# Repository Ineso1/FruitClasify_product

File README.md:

# FruitClasify_product
Creación de un sistema industrial, con el cual se puedan analizar variedad de frutas, para después asignarlas a una categoría por medio de una clasificación bajo ciertos parámetros/características que estas vayan cumpliendo durante el proceso.

**Demo proyecto**
https://drive.google.com/drive/folders/1sFi9FZ5CYVEdVZt0g3_yMmRyJmRK-tTw?usp=sharing

**Sistema camara y sensores**<br></br>!

**Circuito Logico** <br></br>
diseño y simulacion de circuito logico utilizando logica combinacional y logica secuencial con flipflop, multiplexores y full adders

**Cloud computing para procesamiento de imagen**<br></br>
Se crea un servicio con Nodejs para la escucha de peticiones de procesamiento de imagen para la obtencion del tamaño (diametro y area), porcentage BGR de las matrices de colores de la imagen
El procesamiento de imagen se realiza generando un hilo como subproceso del servidor ejecutando scripts de python con OpenCV

**Sistema fisico**
Trasporte por medio de banda transportadora

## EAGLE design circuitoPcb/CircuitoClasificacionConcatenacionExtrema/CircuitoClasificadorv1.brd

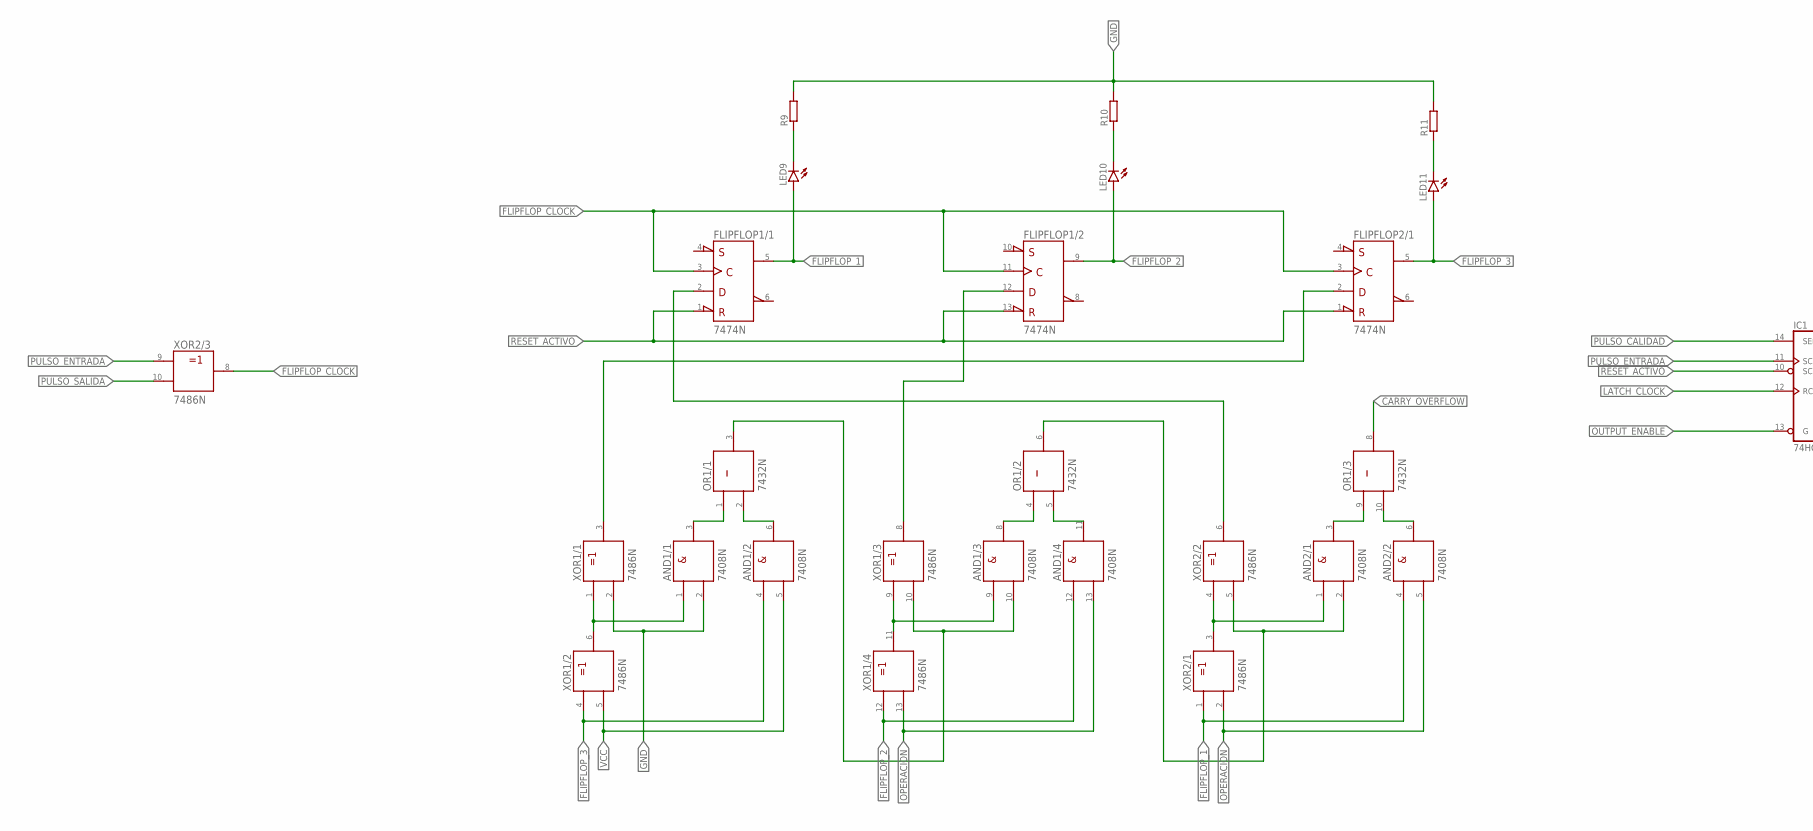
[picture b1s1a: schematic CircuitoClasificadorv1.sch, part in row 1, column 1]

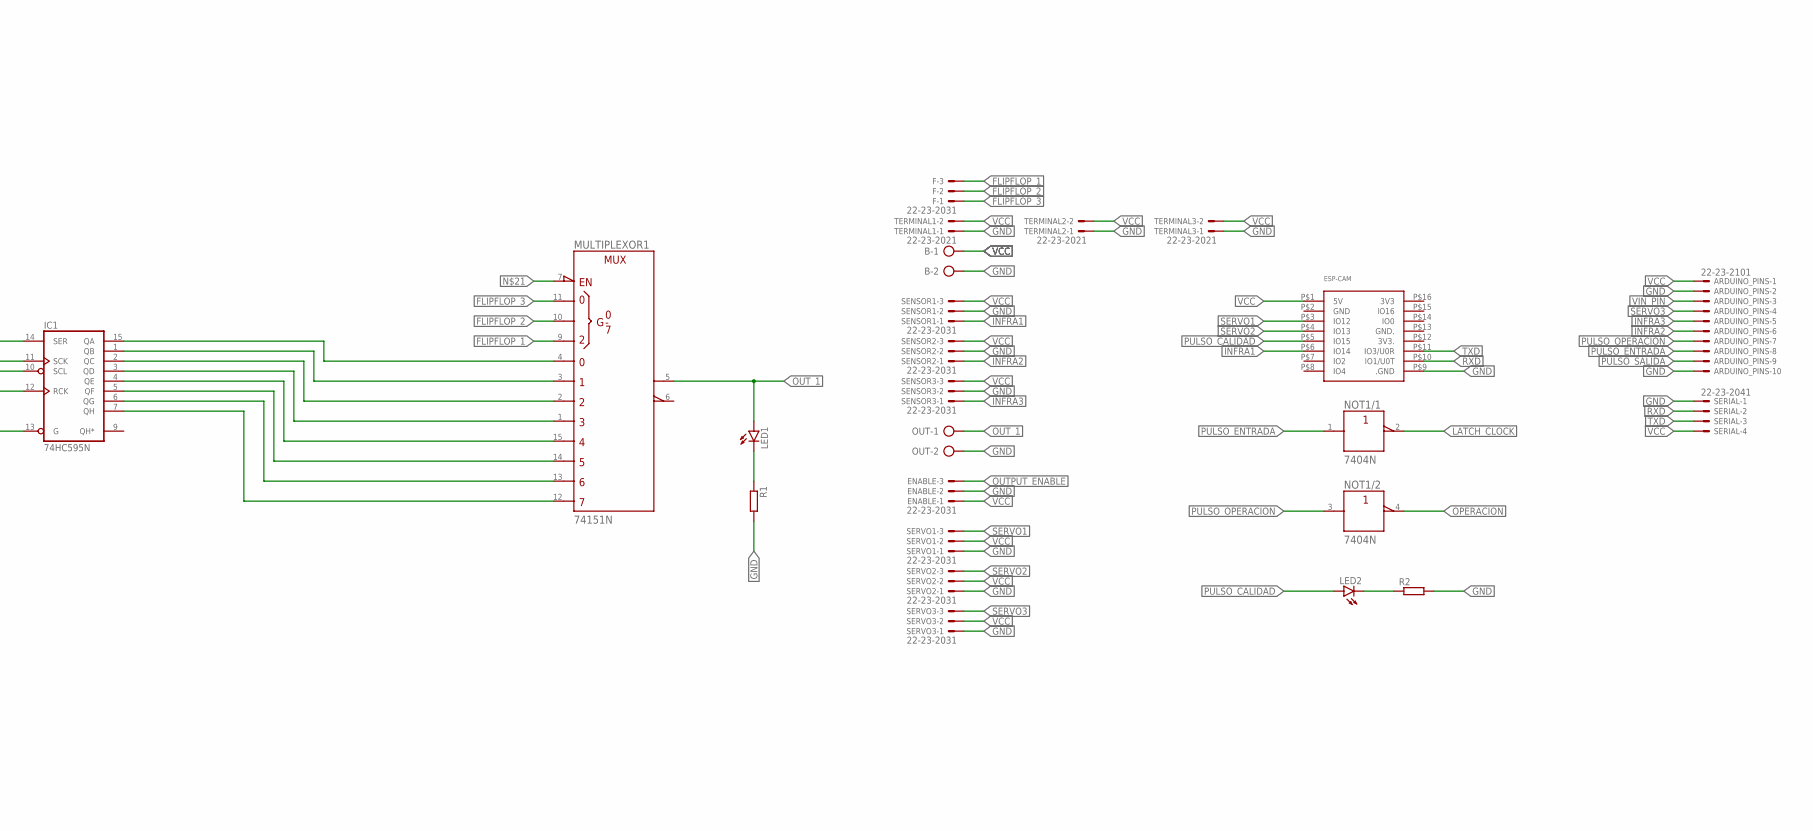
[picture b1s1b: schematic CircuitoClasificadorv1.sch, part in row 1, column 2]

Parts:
AND1, AND2: 7408N; DIL14
ARDUINO_PINS: 22-23-2101
B: AK500/2
ENABLE: 22-23-2031
ESP-CAM: ESP32-CAM
F: 22-23-2031
FLIPFLOP1, FLIPFLOP2: 7474N; DIL14
IC1: 74HC595N; DIL16
LED1, LED2, LED9, LED10, LED11: LED5MM
MULTIPLEXOR1: 74151N; DIL16
NOT1: 7404N; DIL14
OR1: 7432N; DIL14
OUT: AK500/2-H
R1, R2, R9, R10, R11: R-EU_0207/10; 0207/10
SENSOR1, SENSOR2, SENSOR3: 22-23-2031
SERIAL: 22-23-2041
SERVO1, SERVO2, SERVO3: 22-23-2031
TERMINAL1, TERMINAL2, TERMINAL3: 22-23-2021
XOR1, XOR2: 7486N; DIL14

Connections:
+UB: AND1.14 (+UB), AND2.14 (+UB), FLIPFLOP1.14 (+UB), FLIPFLOP2.14 (+UB), MULTIPLEXOR1.16 (+UB), NOT1.14 (+UB), OR1.14 (+UB), XOR1.14 (+UB), XOR2.14 (+UB)
-UB: AND1.7 (-UB), AND2.7 (-UB), FLIPFLOP1.7 (-UB), FLIPFLOP2.7 (-UB), MULTIPLEXOR1.8 (-UB), NOT1.7 (-UB), OR1.7 (-UB), XOR1.7 (-UB), XOR2.7 (-UB)
CARRY_OVERFLOW: OR1.8 (Y)
FLIPFLOP_1: AND2.4 (A), F.3, FLIPFLOP1.5 (Q), LED9.A, MULTIPLEXOR1.9 (C), XOR2.1 (A)
FLIPFLOP_2: AND1.12 (A), F.2, FLIPFLOP1.9 (Q), LED10.A, MULTIPLEXOR1.10 (B), XOR1.12 (A)
FLIPFLOP_3: AND1.4 (A), F.1, FLIPFLOP2.5 (Q), LED11.A, MULTIPLEXOR1.11 (A), XOR1.4 (A)
FLIPFLOP_CLOCK: FLIPFLOP1.3 (CLK), FLIPFLOP1.11 (CLK), FLIPFLOP2.3 (CLK), XOR2.8 (Y)
GND: AND1.2 (B), ARDUINO_PINS.2, ARDUINO_PINS.10, B.2, ENABLE.2, ESP-CAM.P$9 (.GND), IC1.8 (GND), OUT.2, R1.2, R2.2, R9.2, R10.2, R11.2, SENSOR1.2, SENSOR2.2, SENSOR3.2, SERIAL.1, SERVO1.1, SERVO2.1, SERVO3.1, TERMINAL1.1, TERMINAL2.1, TERMINAL3.1, XOR1.2 (B)
INFRA1: ESP-CAM.P$6 (IO14), SENSOR1.1
INFRA2: ARDUINO_PINS.6, SENSOR2.1
INFRA3: ARDUINO_PINS.5, SENSOR3.1
LATCH_CLOCK: IC1.12 (RCK), NOT1.2 (Y)
unnamed: AND1.1 (A), XOR1.1 (A), XOR1.6 (Y)
unnamed: LED2.K (C), R2.1
unnamed: LED1.K (C), R1.1
unnamed: AND1.6 (Y), OR1.2 (B)
unnamed: FLIPFLOP2.2 (D), XOR1.3 (Y)
unnamed: AND1.3 (Y), OR1.1 (A)
unnamed: AND1.8 (Y), OR1.4 (A)
unnamed: AND1.11 (Y), OR1.5 (B)
unnamed: AND1.9 (A), XOR1.9 (A), XOR1.11 (Y)
unnamed: AND1.10 (B), OR1.3 (Y), XOR1.10 (B)
unnamed: AND2.3 (Y), OR1.9 (A)
unnamed: AND2.6 (Y), OR1.10 (B)
unnamed: AND2.1 (A), XOR2.3 (Y), XOR2.4 (A)
unnamed: AND2.2 (B), OR1.6 (Y), XOR2.5 (B)
unnamed: FLIPFLOP1.12 (D), XOR1.8 (Y)
unnamed: FLIPFLOP1.2 (D), XOR2.6 (Y)
unnamed: IC1.15 (QA), MULTIPLEXOR1.4 (D0)
unnamed: IC1.1 (QB), MULTIPLEXOR1.3 (D1)
unnamed: IC1.2 (QC), MULTIPLEXOR1.2 (D2)
unnamed: IC1.3 (QD), MULTIPLEXOR1.1 (D3)
unnamed: IC1.4 (QE), MULTIPLEXOR1.15 (D4)
unnamed: IC1.5 (QF), MULTIPLEXOR1.14 (D5)
unnamed: IC1.6 (QG), MULTIPLEXOR1.13 (D6)
unnamed: IC1.7 (QH), MULTIPLEXOR1.12 (D7)
unnamed: LED11.K (C), R11.1
unnamed: LED10.K (C), R10.1
unnamed: LED9.K (C), R9.1
OPERACION: AND1.13 (B), AND2.5 (B), NOT1.4 (Y), XOR1.13 (B), XOR2.2 (B)
OUTPUT_ENABLE: ENABLE.3, IC1.13 (G)
OUT_1: LED1.A, MULTIPLEXOR1.5 (Y), OUT.1
PULSO_CALIDAD: ESP-CAM.P$5 (IO15), IC1.14 (SER), LED2.A
PULSO_ENTRADA: ARDUINO_PINS.8, IC1.11 (SCK), NOT1.1 (A), XOR2.9 (A)
PULSO_OPERACION: ARDUINO_PINS.7, NOT1.3 (A)
PULSO_SALIDA: ARDUINO_PINS.9, XOR2.10 (B)
RESET_ACTIVO: FLIPFLOP1.1 (!CLR), FLIPFLOP1.13 (!CLR), FLIPFLOP2.1 (!CLR), IC1.10 (SCL)
RXD: ESP-CAM.P$10 (IO1/U0T), SERIAL.2
SERVO1: ESP-CAM.P$3 (IO12), SERVO1.3
SERVO2: ESP-CAM.P$4 (IO13), SERVO2.3
SERVO3: ARDUINO_PINS.4, SERVO3.3
TXD: ESP-CAM.P$11 (IO3/U0R), SERIAL.3
VCC: AND1.5 (B), ARDUINO_PINS.1, B.1, ENABLE.1, ESP-CAM.P$1 (5V), IC1.16 (VCC), SENSOR1.3, SENSOR2.3, SENSOR3.3, SERIAL.4, SERVO1.2, SERVO2.2, SERVO3.2, TERMINAL1.2, TERMINAL2.2, TERMINAL3.2, XOR1.5 (B)
VIN_PIN: ARDUINO_PINS.3

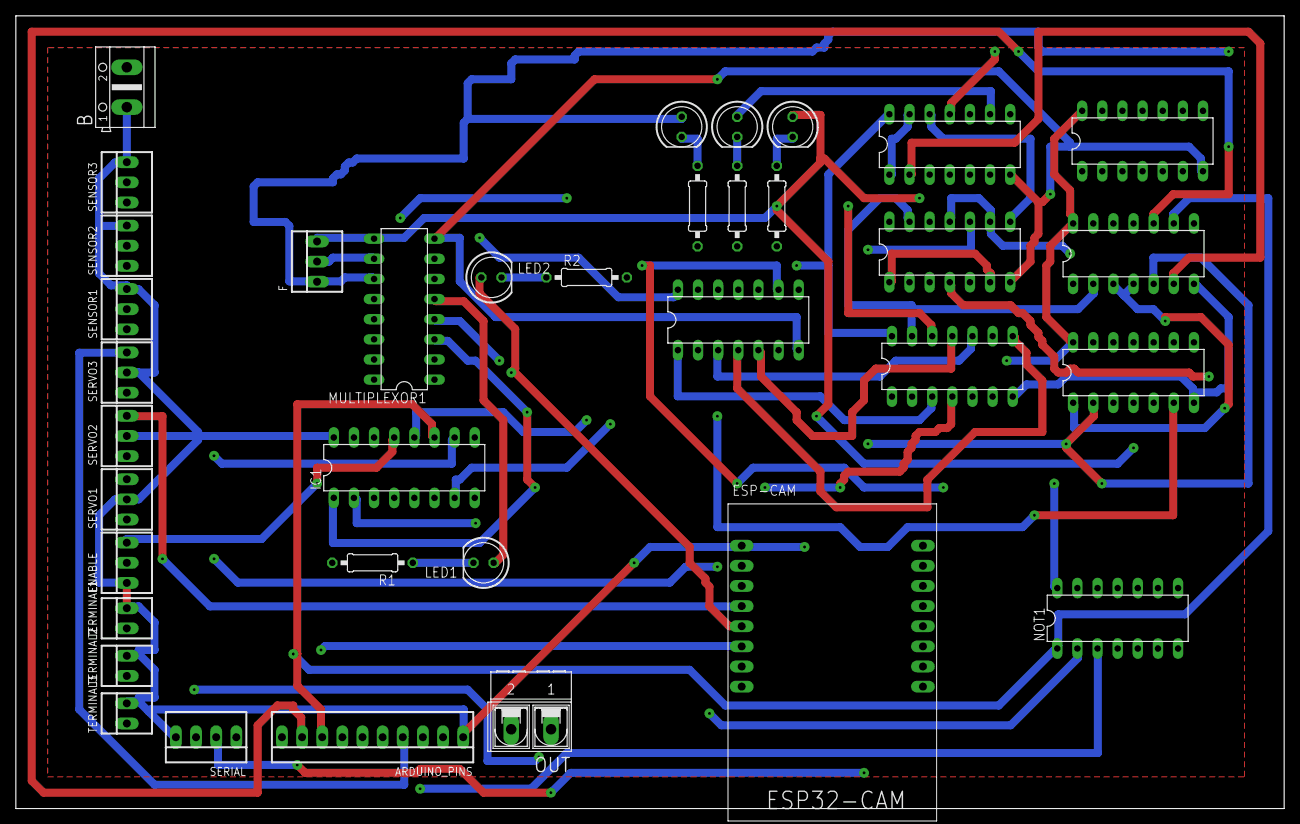
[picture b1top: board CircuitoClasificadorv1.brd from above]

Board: 4 copper layers, 160.0 x 100.0 mm, 36 parts (0 on the bottom side), 52 nets.

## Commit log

2022-12-02 Primera entrega clasificador
2023-01-13 scripts prueba procesamiento de imagen
2023-01-13 pruebas de procesamiento de imagen
